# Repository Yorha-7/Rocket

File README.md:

# Rocket — a from-scratch simulator for actively-guided model rockets

This repo is one project told in three layers: a **physics simulation** that
predicts how a rocket actually flies, a **flight-computer stack** (sensors +
guidance + a gimbaled nozzle) that steers it, and the **hardware** (PCB,
motor, airframe) that would eventually fly for real. The simulation
(`sim/rocket_cpp/`) is the part that's actually working today and the focus of
this document.

If you don't have an aerospace background, that's fine — every technical
term below is explained the first time it shows up, and **[Appendix A](#appendix-a--glossary)**
is a full glossary you can jump to any time something's unclear.

## Table of contents

- [Why this project exists](#why-this-project-exists)
- [The big picture](#the-big-picture)
- [Stage 1 — `ork/`: reading the rocket back out of OpenRocket](#stage-1--ork-reading-the-rocket-back-out-of-openrocket)
- [Stage 2 — `sim/`: the physics engine](#stage-2--sim-the-physics-engine)
- [Stage 3 — `gnc/`: sensors, guidance, and the gimbal](#stage-3--gnc-sensors-guidance-and-the-gimbal)
- [What one simulated flight actually does](#what-one-simulated-flight-actually-does)
- [The hardware side](#the-hardware-side)
- [Getting started](#getting-started)
- [Interception analysis](#interception-analysis)
- [Honest limitations](#honest-limitations)
- [Where to go deeper](#where-to-go-deeper)
- [Appendix A — Glossary](#appendix-a--glossary)
- [Appendix B — Repository map](#appendix-b--repository-map)

## Why this project exists

[OpenRocket](https://openrocket.info/) is the standard free tool for
designing and simulating model rockets — you build up a rocket's geometry
(nose cone, body tube, fins), pick a motor, and it simulates the flight for
you. It's excellent at that. But it only simulates **passive** flight: the
rocket is a fixed shape with fixed fins, and the only thing steering it is
whatever natural aerodynamic stability that shape has. There's no way to
model a rocket that can sense its own attitude and *actively* push itself
back on course mid-flight.

That's exactly the gap this project fills. The goal was a rocket that
carries a **gimbaled** (steerable) nozzle — one that can tilt the direction
of its thrust in real time, the same basic idea SpaceX boosters use — and
a small onboard "brain" that decides, moment to moment, which way to point
it so the rocket flies toward a chosen target instead of wherever its fins
happen to point it.

Since no existing free tool simulates that, the design here uses each tool
for what it's actually good at:

- **OpenRocket** stays the design tool. The airframe geometry and motor
  choice are still built and exported there, as a `.ork` file — no reason
  to reinvent rocket CAD.
- **Everything downstream of that** — reading the design back out,
  computing how it actually flies, and closing the steering loop — is a
  custom C++ simulator (`sim/rocket_cpp/`), built from scratch, because that
  piece genuinely didn't exist anywhere else.

## The big picture

The simulator is organized into three modules that mirror three physically
distinct jobs. Each one lives in its own folder under `sim/rocket_cpp/include/`
and `sim/rocket_cpp/src/`:

```mermaid
flowchart LR
    ork(["rocket.ork<br/>geometry, motor thrust &amp; mass curve"])

    subgraph SIM["sim/ — physics engine"]
        physics["own aero coefficients<br/>own kinematics &amp; torques"]
    end

    subgraph GNC["gnc/ — flight computer"]
        direction TB
        sensors["Sensors"] --> nav["Navigation<br/>(guidance)"] --> tvc["ThrustVectorControl"]
    end

    ork -->|"ork/"| physics
    physics -->|"vehicle state"| sensors
    tvc -->|"nozzle angle"| physics
```

- **`ork/`** — a `.ork` file is really just a zip archive containing XML
  (OpenRocket's save format). This module unzips it and reads out the
  rocket's shape and its motor's thrust/mass-over-time curve.
- **`sim/`** — the **ground-truth physics engine**. Given the vehicle's
  shape and how the nozzle is currently pointed, this is what actually
  computes forces, torques, and the resulting motion, step by step.
- **`gnc/`** — short for **Guidance, Navigation, and Control**, the
  standard aerospace term for "the flight computer stack." This is the
  part that watches where the rocket is and decides how to move the
  nozzle to correct course — the actively-controlled half of the project
  that OpenRocket has no equivalent of at all.

Every step of simulated flight flows through all three: `sim/` computes
"what actually happened this instant," `gnc/` reads that and decides "what
to do next," and that decision feeds back into `sim/` for the following
step. That feedback loop — measure, decide, act, repeat — is what
**closed-loop control** means, and it's the whole reason this project
exists.

## Stage 1 — `ork/`: reading the rocket back out of OpenRocket

OpenRocket's own file format bundles everything about a design into one
`.ork` file: body dimensions, nose shape, fin geometry, and — if you've run
a simulation inside OpenRocket itself — a full time history of that flight
too.

This project only trusts **one** thing out of that file: the motor's own
**thrust curve** (thrust in newtons over time) and **mass curve** (how much
the vehicle weighs as it burns propellant). That data comes from the motor
manufacturer's own testing, not from OpenRocket's simulation, so there's no
substitute for it — a solid rocket motor's thrust profile isn't something
you can derive from first principles without literally burning one on a
test stand.

Everything else about *how the rocket flies* — drag, stability, the
turning forces air exerts on it — is deliberately **not** read from
OpenRocket's own simulated results. It's recomputed independently in
Stage 2, from the raw geometry alone. That was a real design decision, not
laziness: this project needed those numbers available live, every physics
step, responding to whatever the guidance system was doing to the vehicle
at that instant — not a fixed, pre-solved number that assumed a passive,
unguided flight.

## Stage 2 — `sim/`: the physics engine

This is the part that answers "given everything about the rocket right
now, what happens in the next instant?" It runs every simulated step and
knows nothing about guidance at all — it just faithfully computes physics
from whatever nozzle angle it's told.

**Forces.** Three things push and pull on the rocket:
- **Thrust**, from the motor, redirected by however much the nozzle is
  currently tilted (see Stage 3).
- **Drag**, opposing whatever direction the rocket is actually moving.
  Computed from **dynamic pressure** (`q = ½ρv²` — a measure of how hard
  the air is pushing, from air density `ρ` and airspeed `v`) times a drag
  coefficient.
- **Gravity**, pulling straight down, scaled by the vehicle's
  current mass (which drops as the motor burns fuel).

**Where the drag/turning coefficients come from.** The air-density and
speed-of-sound model is the **ISA** (International Standard Atmosphere —
the standard formula relating altitude to pressure, temperature, and
density). The aerodynamic coefficients themselves — how much drag, and how
much sideways "normal force," a given shape produces — come from the
**Barrowman method**, a set of formulas (from a 1966 NASA-adjacent paper
by James Barrowman) that predict a model rocket's aerodynamics directly
from its geometry: nose shape, fin count and shape, body diameter. It also
computes the **center of pressure (CP)** — the single point where all that
aerodynamic force can be treated as acting — purely from geometry.

**Why the rocket tips over on its own.** Every rigid body has a
**center of gravity (CG)** — the point where its mass balances — and, for
an aerodynamic body, that's normally in a different place than the CP. If
the two are offset and the rocket's nose isn't pointed exactly along its
direction of travel, that mismatch is called **angle of attack (α)** (in
the fore-aft plane) and **sideslip (β)** (in the left-right plane) — and
the aerodynamic force acting through the offset CP creates a **torque**
(a rotational force, a twist) around the CG that tries to swing the nose
back into the airflow. This self-correcting behavior is called
**weathercocking** — the same reason a weathervane always points into the
wind — and it's why a well-designed *passive* rocket (no guidance at all)
still flies straight. This simulation models that torque for real,
opposed by an aerodynamic **damping** torque (resistance proportional to
how fast the rocket is already rotating, so it settles instead of
oscillating forever), the same way OpenRocket's own flight model does.

**Turning that into motion.** Each step: sum the forces, divide by mass to
get acceleration, integrate that into velocity and position (a numerical
integration scheme called **Euler integration** — approximate the next
instant using the current rate of change, repeated thousands of times a
second). Sum the torques, divide by **moment of inertia** (a body's
resistance to being spun, the rotational equivalent of mass) to get
angular acceleration, and integrate that into rotation rate and
orientation (pitch and yaw **Euler angles** — the standard "tip
forward/back" and "swing left/right" attitude angles).

Translating between "the rocket's own point of view" (body frame — where
+Z is the direction the nose is pointing) and "the world's point of view"
(world frame — where +Z is straight up) is done with a rotation matrix
called a **DCM** (Direction Cosine Matrix) built from those Euler angles.
Thrust and drag are computed in the body frame (they naturally act along
and against the vehicle's own axes) and then rotated into the world frame
to actually move the rocket through space.

## Stage 3 — `gnc/`: sensors, guidance, and the gimbal

This is the layer with no OpenRocket equivalent — the part that makes
this a *controlled* rocket instead of a passive one. Three pieces, each
modeling a real physical part of a flight computer:

**Sensors** (`Gyro`, `Baro`, `Gps`) — simulated readings of the vehicle's
own true state: orientation and rotation rate (gyroscope), altitude
(barometer), and position (GPS). Today they read the simulation's own
ground truth directly, with no noise or bias modeled yet — the point is
to keep the *interface* realistic (a real flight computer can only ever
act on what its sensors report, never on the world's actual state
directly) so sensor imperfection can be layered in later without
restructuring anything above it.

**Navigation** — the guidance law. Every step, it works out the angle
between where the nose is currently pointing and the direction to the
target, and shapes that error through a **PID controller** — the standard
feedback-control building block, one of the most widely used in all of
engineering. Its three terms:
- **P** (proportional) — command is bigger when the error is bigger,
  smaller when it's smaller. The straightforward "steer toward the
  target harder the more off-course you are" behavior.
- **I** (integral) — accumulates error over time, so a small but
  *persistent* error that P alone can't fully correct still eventually
  gets cleaned up.
- **D** (derivative) — reacts to the *rate* the error is changing, to
  damp out overshoot before it happens.

In this project's tuning, **D turned out to hurt**, not help — because
the gimbal actuator (next paragraph) already has its own built-in damping
from its physical lag, so an extra derivative term on top of it just
fought the correction instead of smoothing it. That's a real finding from
testing this specific vehicle, not a rule that holds for every control
system — see [`sim/rocket_cpp/include/gnc/navigation.hpp`](./sim/rocket_cpp/include/gnc/navigation.hpp)
for the actual numbers. Navigation also deliberately stays off below a
minimum altitude — right off the pad, a tiny angle error would otherwise
translate into a full steering command at the worst possible moment.

Navigation is now split into two classes: `Navigation` (a simple path
planner — breaks one final target into a straight-line sequence of
nearby waypoints) driving `NavigationStep` (the PID controller described
above) one waypoint at a time. The reason: a target close to the pad and
one far downrange ask the same fixed gain set for very different
maneuvers, so instead of retuning per-target, the planner makes every
step look like the same kind of local steering problem — see
[`sim/rocket_cpp/include/gnc/navigation.hpp`](./sim/rocket_cpp/include/gnc/navigation.hpp).
`sim/rocket_cpp/src/tuning/` is a separate, offline tool (`pid_ga_tuner`) that
searches for a better (Kp, Ki, Kd) triple than manual tuning found — three
binary-encoded genetic algorithms, one per gain, run concurrently and
coordinating through a shared live "current best" value rather than each
working in isolation. See
[`sim/rocket_cpp/README.md`](./sim/rocket_cpp/README.md#tuning-navigationsteps-gains-with-a-genetic-algorithm)
for the full design.

**ThrustVectorControl (TVC)** — the actuator model for the nozzle itself.
Commanding a new angle doesn't make the physical nozzle teleport there; a
real servo eases toward a new position over a fraction of a second. This
is modeled as a **first-order lag** (the standard way to represent "eases
toward a target, doesn't jump") with a real travel limit (the nozzle can
only physically tilt so far). That lag is what actually produces the
thrust direction Stage 2's physics engine reads each step.

## What one simulated flight actually does

Put together, one simulated second looks like this, repeated at the
integrator's time step:

1. **Sim** computes this instant's forces/torques from the current state
   and however the nozzle is currently angled, and integrates the vehicle
   one step forward.
2. **Sensors** take a fresh reading of that new state (position,
   orientation, rotation rate).
3. **Navigation** compares that to the target and computes a new desired
   thrust direction via its PID law.
4. **TVC** eases the physical nozzle angle toward that new command by
   however far its actuator lag allows in one step.
5. Repeat, until the rocket reaches **apogee** (the highest point of the
   flight, where vertical velocity crosses zero) and comes back down to
   ground contact.

The result is written to a CSV and plotted — a full 3D trajectory, forces
over time, and the commanded vs. actual gimbal angle history:

## The hardware side

The eventual goal is for this to fly on real hardware, not just in
simulation. `artifacts/` and `kiCAD/` hold the in-progress flight-computer
PCB design. The `feat/launcher` branch extends the STM32F103C8T6 board,
which carries an MPU-9250 IMU and an MS5611 pressure sensor, with:

- **microSD card slot** (`J5`, Molex 104031-0811) for onboard flight-data
  storage.
- **Buzzer** (`LS1`, PS1240P02CT3) for audible status and alerts.
- **Two servo headers** (`J1` and `J4`) for the gimbal servos, with a
  dedicated **TPS61033 boost regulator** supplying the servo power rail.
- **Standard 10-pin SWD programming/debug connector** (`J2`, 2×5),
  exposing SWDIO, SWCLK, SWO, and reset for the STM32.
- **Battery terminal and USB-C charging input** (`J6` and `J3`), with a
  **BQ24074 charger and power-path controller** for charging from a USB-C
  adapter and supplying the board from the battery or external input.
- **Status LEDs** for the charging/power circuitry, alongside the existing
  USB-C interface, boot switch, and 3.3 V regulation.

These are schematic and PCB additions; firmware support and bench/flight
validation remain separate work. GPS is modeled in the simulator but is
not fitted to this PCB revision. The KiCad project is
[`kiCAD/schmatic/schmatic.kicad_pro`](./kiCAD/schmatic/schmatic.kicad_pro),
with the schematic and board layout beside it.

An earlier prototype of the trajectory math (before the C++ rewrite) was
built in MATLAB/Simulink — kept in `sim/simulink/` and `sim/matlab/` for history, but
superseded by `sim/rocket_cpp/`, which is now the actively developed
simulation:

## Getting started

The simulator is a standard CMake C++ project. From `sim/rocket_cpp/`:

```bash
cmake -S . -B build
cmake --build build
./build/rocket_cpp
```

This loads `sim/data/rocket.ork`, runs a full guided flight, and writes
`rocket_trajectory.csv` plus plots. See
**[`sim/rocket_cpp/README.md`](./sim/rocket_cpp/README.md)** for the full build
prerequisites and how to point it at a different `.ork`/target.

Every plotting script reads from that same `rocket_trajectory.csv`, so
they all stay in sync with whatever flight was simulated last:

| Script | What it shows | Run it |
|---|---|---|
| `scripts/plot_trajectory.py` | The 7-subplot flight-analysis figure — called automatically at the end of every `./build/rocket_cpp` run, not something you normally run by hand. | `python3 scripts/plot_trajectory.py rocket_trajectory.csv rocket_analysis.png` |
| `scripts/trajectory.py` | The control panel, not just a viewer: an interactive, rotatable 3D flight path (mouse to orbit/zoom) with launch/burnout/apogee/impact/target markers and a pass/fail readout, plus text boxes for target x/y/z and initial tilt/yaw and a Run button that launches a fresh (fast `--preview`) simulation and redraws in place. Pass a CSV path instead to fall back to a plain one-shot viewer, no controls. | `python3 scripts/trajectory.py` |
| `scripts/tvc.py` | The commanded gimbal angle over time, pitch and yaw axes on separate panels — what the nozzle actually did, lag included. | `python3 scripts/tvc.py rocket_trajectory.csv` |
| `scripts/x_force.py` | The net world-frame X-force over time (thrust + drag; gravity has no X-component) — useful for seeing exactly when the motor burns out. | `python3 scripts/x_force.py rocket_trajectory.csv` |
| `scripts/make_axis_diagram.py` | Regenerates the coordinate-frame/TVC reference diagram used above — a docs utility, not a per-flight plot. | `python3 scripts/make_axis_diagram.py` |

## Interception analysis

The active-guidance result is evaluated with a batch interception sweep, not
just one hand-picked trajectory. The sweep samples static targets in the
valid upper hemisphere of a 500 m sphere around the launch point, then records
the rocket's minimum 3D distance to each target. Closest approach is linearly
interpolated between simulation samples so the result is not tied to one
discrete timestep.

The latest full-fidelity terminal-guidance sweep uses 16 radial shells and 96
directions per shell, producing 1,434 valid target cases:

| Metric | Result |
|---|---:|
| Median miss distance | 6.185 m |
| Within 5 m | 606 / 1,434 |
| Within 10 m | 792 / 1,434 |
| Within 25 m | 980 / 1,434 |
| Worst miss distance | 144.068 m |

For comparison, the original waypoint/PID guidance had a 129.3 m median miss
over the same target set. The remaining large misses are concentrated in
far-lateral, very-low-altitude targets where the TVC reaches its 30° travel
limit before the vehicle can build enough lateral velocity.

The data behind this figure is
[interception_results_terminal_dense_full.csv](./sim/rocket_cpp/results/csv/interception_results_terminal_dense_full.csv).
To regenerate the plot after a new sweep:

```bash
cd sim/rocket_cpp
./build/interception_sweep --full --terminal \
  --output results/csv/interception_results_terminal_dense_full.csv
python3 scripts/plot_interception_sweep.py
```

## Honest limitations

This is a staging-area project, not a finished flight-certified system.
Worth knowing before trusting any number out of it:

- **Not full 6DOF.** Roll has no torque model yet — it's tracked but never
  actively influenced by anything.
- **An inherent steering asymmetry.** Because thrust is along the body's
  own vertical axis, sideways (Y-direction) steering authority needs
  *both* pitch and yaw deflected at once, while forward (X-direction)
  steering only needs one — so the vehicle can push harder in some
  directions than others for the same actuator effort. Documented in
  detail in `sim/rocket_cpp/README.md`'s Staging Notes.
  Structural, not a bug to be patched.
- **Yaw is under-damped** relative to pitch in the current tuning — a
  real, quantified finding, also documented in the Staging Notes.
- **Motor burn time is short.** The default demo motor (an AeroTech G61W)
  burns out in about two seconds — meaning TVC only has roughly that long
  to actually influence the trajectory before the rest of the flight is
  unpowered, ballistic coasting no gimbal command can affect. Worth
  knowing before reading too much into how "precise" any single demo run
  looks.
- **GPS noise, once added, exposed a real limitation — partially, not
  fully, addressed.** Sensors carry a real noise model grounded in actual
  hardware specs (see [Stage 3](#stage-3--gnc-sensors-guidance-and-the-gimbal)).
  GPS error drifts over a ~60-second correlation time — comparable to
  this vehicle's whole ~25-second flight — so within any single flight it
  acts like a near-constant few-meter miscalibration rather than noise
  that averages out. `Navigation` now fuses that noisy GPS fix with the
  accelerometer (an alpha-beta filter, gains derived from real sensor
  numbers) instead of reading raw GPS — tested head-to-head, it makes the
  guided trajectory ~10x more repeatable run to run, but doesn't improve
  *average* accuracy, because no amount of filtering can reject a
  persistent bias in the only absolute-position sensor available. That's
  the same limitation every real GPS-only guided system has without a
  second independent sensor backing it up — see `sim/rocket_cpp/README.md`'s
  Staging Notes for the full writeup.

None of these are hidden — see
**[`sim/rocket_cpp/README.md`](./sim/rocket_cpp/README.md#staging-notes)** for the
full, current list, kept up to date as things change.

## Where to go deeper

- **[`sim/rocket_cpp/README.md`](./sim/rocket_cpp/README.md)** — the full
  technical reference: every class and method, the exact math behind each
  physics model, coordinate-frame conventions, build instructions, and a
  running log of bugs found and fixed along the way.
- **[`sim/rocket_cpp/docs/axis_and_tvc_reference.png`](./sim/rocket_cpp/docs/axis_and_tvc_reference.png)**
  — the coordinate-frame and gimbal-geometry diagram referenced above.
- Source is organized along the three-module split described
  above — `sim/rocket_cpp/include/{sim,ork,gnc}/` and
  `sim/rocket_cpp/src/{sim,ork,gnc}/`. The thin executable wrapper lives in
  `sim/rocket_cpp/src/main.cpp`; the single-flight orchestration and TVC test
  sequence loader live in `sim/rocket_cpp/src/simulation_runner.cpp` with its
  public declaration in `sim/rocket_cpp/include/simulation_runner.hpp`.

## Appendix A — Glossary

Terms used throughout this document and the codebase, in plain language.

| Term | Meaning |
|---|---|
| **Angle of attack (α)** | The angle between where the nose points and the direction the vehicle is actually moving through the air, measured fore-aft. Zero when flying nose-first into the wind. |
| **Apogee** | The highest point of a flight — where vertical velocity crosses from positive (rising) to negative (falling). |
| **Barrowman method** | A set of formulas for predicting a rocket's aerodynamic coefficients (drag, stability, center of pressure) directly from its geometry, without wind-tunnel testing. |
| **Body frame** | A coordinate system attached to the rocket itself and rotating with it — "the rocket's own point of view," where its nose axis is always +Z regardless of which way the vehicle is actually pointed in the sky. |
| **CG (center of gravity)** | The single point where a body's mass balances — its "center of mass." |
| **Closed-loop control** | Continuously measuring a system's actual state and adjusting based on that measurement, as opposed to acting on a fixed, pre-planned schedule ("open-loop"). |
| **CP (center of pressure)** | The single point where the net effect of all aerodynamic forces on a body can be treated as acting. |
| **Damping** | A force or torque that resists motion in proportion to how fast that motion is already happening — what settles an oscillation down instead of letting it continue forever. |
| **DCM (Direction Cosine Matrix)** | A 3×3 rotation matrix used to convert a vector from one coordinate frame to another (e.g., body frame to world frame). |
| **DOF (degrees of freedom)** | How many independent ways a system can move. 3DOF = position in x/y/z only; 6DOF adds all three rotational axes (roll/pitch/yaw) too. |
| **Dynamic pressure (q)** | `q = ½ρv²` — a measure of how hard oncoming air pushes on a body, from air density (ρ) and airspeed (v). The basis for computing drag and other aerodynamic forces. |
| **Euler angles** | The standard roll/pitch/yaw representation of a rigid body's orientation — how far it's tipped, tilted, and turned from some reference orientation. |
| **Euler integration** | A numerical method for simulating motion: approximate what happens next using the current rate of change, over a small time step, repeated many times. |
| **First-order lag** | A system that eases toward a new target value exponentially over time rather than jumping there instantly — the standard model for how a real physical actuator (like a servo) responds to a new command. |
| **Gimbal** | A pivoting mount that lets something (here, a rocket engine's nozzle) tilt independently of the body it's attached to. |
| **GNC (Guidance, Navigation, and Control)** | The standard aerospace term for the combined sense-decide-act subsystem of a vehicle — in this project, the `gnc/` module (sensors, `Navigation`, and `ThrustVectorControl`). |
| **Integral windup** | A failure mode of the "I" term in a PID controller: if error persists for a long time (e.g., an actuator pinned at its limit), the accumulated integral can grow very large and cause a big overshoot once the error finally starts shrinking. Usually prevented by clamping the accumulator. |
| **ISA (International Standard Atmosphere)** | A standard reference model relating altitude to air pressure, temperature, and density. |
| **Moment of inertia** | A body's resistance to being rotated — the rotational equivalent of mass. |
| **Normal force** | The aerodynamic force acting perpendicular to a body's own axis (as opposed to axial force/drag, which acts along it) — what actually turns a rocket, not what slows it down. |
| **PID controller** | A feedback-control law combining Proportional (react to current error), Integral (react to accumulated past error), and Derivative (react to how fast error is changing) terms — one of the most common control algorithms in engineering. |
| **Sideslip (β)** | The same idea as angle of attack, but measured left-right instead of fore-aft. |
| **Stability margin / weathercocking** | The natural tendency of a well-designed (finned) rocket to turn its nose back into the oncoming airflow on its own, the same way a weathervane points into the wind — the reason passive, unguided rockets can fly straight at all. |
| **Torque (moment)** | A rotational force — a twist applied around some pivot point, as opposed to a straight-line push. |
| **TVC (Thrust Vector Control)** | Steering a vehicle by tilting the direction of its engine thrust, rather than (or in addition to) aerodynamic surfaces like fins. |
| **World frame** | A coordinate system fixed to the ground/launch site — "the outside observer's point of view," as opposed to the body frame, which moves and rotates with the rocket. |

## Appendix B — Repository map

```
Rocket/
├── sim/                 all simulation-only code, models, data, and docs
│   ├── rocket_cpp/      active simulation engine (see its own README.md)
│   │   ├── include/{sim,ork,gnc}/ headers, one folder per module
│   │   ├── src/{sim,ork,gnc}/     implementation, mirrors include/
│   │   ├── scripts/               Python plotting and analysis
│   │   └── data/                  TVC test sequences
│   ├── data/            shared OpenRocket and motor inputs
│   ├── simulink/        early Simulink prototype
│   ├── matlab/          early MATLAB support files
│   └── docs/            generated simulator manuals
├── artifacts/            hardware renders and component references
├── kiCAD/                flight-computer PCB design source
└── README.md              whole-project overview
```

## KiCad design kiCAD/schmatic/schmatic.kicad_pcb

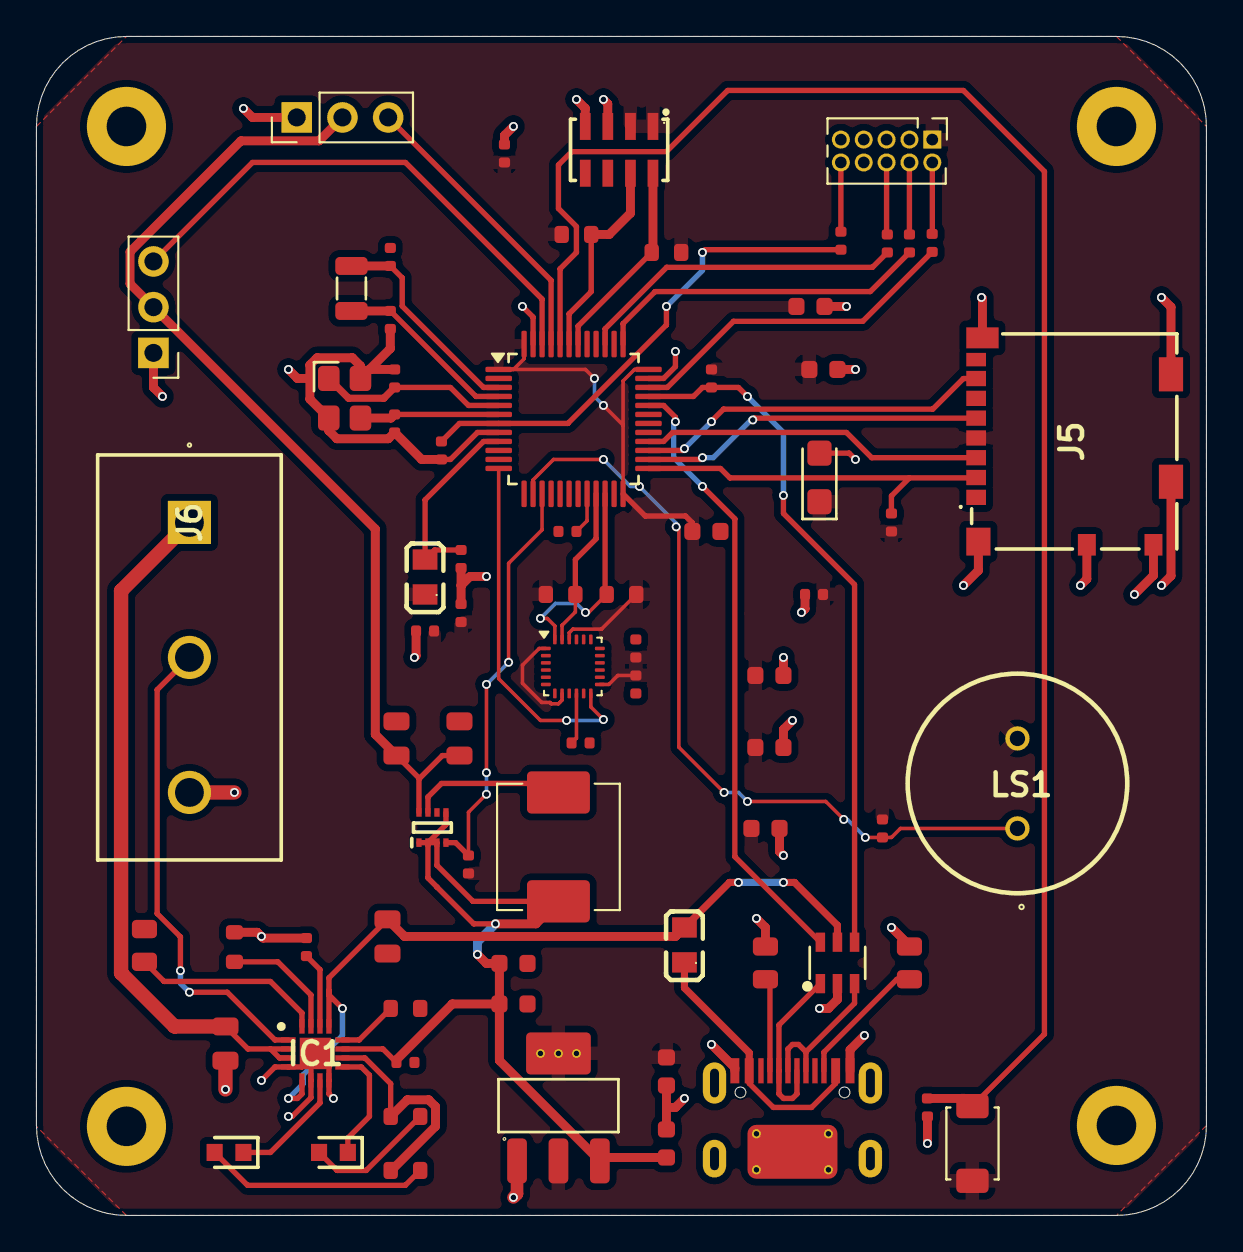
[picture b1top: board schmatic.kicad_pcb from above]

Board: 2 copper layers, 65.0 x 65.5 mm, 77 parts (0 on the bottom side), 52 nets.

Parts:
C1, C2, C3, C4, C5, C9: 4.7uF; C_0603
C6, C15, C26, C27: 10uF; C_0603
C7, C8: 15pF; C_0402
C10, C13, C14, C16, C18, C22, C24: 100nF; C_0402
C11, C12, C25: 10pF; C_0402
C17: 1uF; C_0402
C19: 10uF; C_CASE-A-3216-18(mm)
C20, C21: 10uF; C_0805
C23: 10nF; C_0402
C28, C29: 22uF; C_0805
D1: USBLC6-4SC6; SOT-23-6_L2.9-W1.6-P0.95-LS2.8-BL
H1, H2, H3, H4: MountingHole; MountingHole_2.2mm_M2_Pad
IC1: BQ24074RGTT; QFN50P300X300X100-17N-D
J1, J4: Conn_01x03_Socket; PinHeader_1x03_P2.54mm_Vertical
J2: Conn_02x05_Odd_Even; PinHeader_2x05_P1.27mm_Vertical
J3: Connector, USB-TYPE-C-16P; TYPE-C-SMD_HX-TYPE-C-16PIN
J5: 104031-0811; 1040310811
J6: TB004-750-03GR
L1, L2: GZ2012D121TF; L0805
L3: L; L_APV_APH0620
LED1, LED2: LTST-C190KGKT; LEDC1608X80N
LS1: PS1240P02CT3; PS1240P02BT
PS1: TPS61033DRLR; SOTFL50P160X60-8N
R1, R2, R3, R7: 10kΩ; R_0603
R4, R5: 5.1kΩ; R_0805
R6, R9, R10, R22: 10kΩ; R_0402
R8, R11: 1.5kΩ; R_0402
R12, R13, R14, R15: 22Ω; R_0402
R16, R17, R20, R21: 1.1kΩ; R_0603
R18: 750Ω; R_0805
R19: 49.9kΩ; R_0402
S1: Tactile Button, 160gf; SW_TS-1088-AR02016
U1: AMS1117; SOT-223-3_L6.5-W3.4-P2.30-LS7.0-BR
U2: MS561101BA03-50; SENSORS-SMD_MS5611-01BA03
U4: MPU-9250; InvenSense_QFN-24_3x3mm_P0.4mm
U6: STM32F103C8T6; LQFP-48_7x7mm_P0.5mm
X1: X322516MLB4SI; OSC-SMD_4P-L3.2-W2.5-BL
X2: Q13FC1350000400; FC-135R_L3.2-W1.5

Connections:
+3.3VA: C13.1, L2.2, U6.9 (VDDA)
+3.3VP: C1.1, C2.1, C3.1, C4.1, C5.1, C6.1, C9.1, C10.1, C14.1, C16.1, C17.1, C19.1, C22.1, C23.1, J2.1, J5.4 (VDD), L2.1, LS1.2, R1.1, R2.1, R3.1, R7.1, R8.1, R10.1, R11.1, R22.2, S1.1 (A), U1.2 (VOUT), U1.4 (VOUT), U2.1 (VDD), U2.2 (PS), U4.1 (RESV_VDDIO), U4.8 (VDDIO), U4.13 (VDD), U4.22 (~CS), U6.1 (VBAT), U6.24 (VDD), U6.36 (VDD), U6.48 (VDD)
+5V: C20.1, D1.5, IC1.5 (EN2), IC1.13 (IN), L1.2
+5VD: C28.1, C29.1, J1.2, J4.2, PS1.8 (VOUT)
/BAT+: C21.1, IC1.2 (BAT_1), IC1.3 (BAT_2), J6.1
/Boot0: R6.2, S1.2 (B), U6.44 (BOOT0)
/Boot1: R9.2, U6.20 (PB2)
/CD/DAT3: J5.2 (CD/DAT3), R10.2, U6.25 (PB12)
/CHG: IC1.9 (~CHG), LED2.1 (K)
/D+: D1.4, R8.2, U6.33 (PA12)
/D-: D1.6, U6.32 (PA11)
/DD+: D1.3, J3.A6 (D+), J3.B6 (D+)
/DD-: D1.1, J3.A7 (D-), J3.B7 (D-)
/HSE_IN: C11.1, U6.5 (PD0), X1.1 (OSC)
/HSE_OUT: C12.1, U6.6 (PD1), X1.3 (OSC)
/ILIM: IC1.12 (ILIM), R16.1
/INT: U4.12 (INT), U6.12 (PA2)
/ITERM: IC1.15 (ITERM), R17.1
/LSE_IN: C7.1, U6.3 (PC14), X2.1
/LSE_OUT: C8.1, U6.4 (PC15), X2.2
/MPU_SCL: R2.2, U4.23 (SCL/SCLK), U6.21 (PB10)
/MPU_SDA: R1.2, U4.24 (SDA/MOSI), U6.22 (PB11)
/NRST: C18.1, R15.2, U6.7 (NRST)
/PG: PS1.4 (PG), R22.1, U6.15 (PA5)
/PGOOD: IC1.7 (~PGOOD), LED1.1 (K)
/P_SCL: R3.2, U2.8 (SCLK), U6.42 (PB6)
/P_SDA: R7.2, U2.7 (SDI/SDA), U6.43 (PB7)
/R-ISET: IC1.16 (ISET), R18.1
/S0: J1.3, U6.45 (PB8)
/S1: J4.3, U6.46 (PB9)
/SPI2_MISO: J5.7 (DAT0), U6.27 (PB14)
/SPI2_MOSI: J5.3 (CMD), U6.28 (PB15)
/SPI2_SCK: J5.5 (CLK), U6.26 (PB13)
/SW: L3.2, PS1.7 (SW)
/SWCLK: R13.2, U6.37 (PA14)
/SWDIO: R12.2, U6.34 (PA13)
/SWO: R14.2, U6.39 (PB3)
/TMR: IC1.14 (TMR), R19.1
/TS: IC1.1 (TS), J6.2
/buzzer: LS1.1, R11.2, U6.14 (PA4)
GND: C1.2, C2.2, C3.2, C4.2, C5.2, C6.2, C7.2, C8.2, C9.2, C10.2, C11.2, C12.2, C13.2, C14.2, C15.2, C16.2, C17.2, C18.2, C19.2, C20.2, C21.2, C22.2, C23.2, C24.2, C25.2, C26.2, C27.2, C28.2, C29.2, D1.2, IC1.4 (~CE), IC1.6 (EN1), IC1.8 (VSS), IC1.17 (EP), J1.1, J2.3, J2.5, J2.9, J3.A12B1 (GND), J3.B12A1 (GND), J3.S1 (SHIELD), J4.1, J5.6 (VSS), J5.9, J5.10, J5.11, J5.12, J5.13, J5.14, J6.3, PS1.6 (GND), R4.2, R5.2, R6.1, R9.1, R16.2, R17.2, R18.2, R19.2, U1.1 (GND), U2.3 (GND), U2.4 (CSB), U4.9 (AD0/MISO), U4.11 (FSYNC), U4.18 (GND), U4.20 (RESV_GND), U6.8 (VSSA), U6.23 (VSS), U6.35 (VSS), U6.47 (VSS), X1.2 (GND), X1.4 (GND)
unnamed: J2.2, R12.1
unnamed: J2.4, R13.1
unnamed: J2.6, R14.1
unnamed: J2.10, R15.1
unnamed: J3.A5 (CC1), R5.1
unnamed: J3.B5 (CC2), R4.1
unnamed: J3.A9B4 (VBUS), J3.B9A4 (VBUS), L1.1
unnamed: LED1.2 (A), R21.1
unnamed: LED2.2 (A), R20.1
unnamed: C24.1, U4.10 (REGOUT)
VDD: C15.1, C25.1, C26.1, C27.1, IC1.10 (OUT_1), IC1.11 (OUT_2), L3.1, PS1.1 (VIN), PS1.2 (EN), PS1.3 (MODE), PS1.5 (FB), R20.2, R21.2, U1.3 (VIN)
